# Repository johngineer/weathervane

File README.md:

# weathervane

Weathervane Digital Readout Hardware

February 1-2, 2015 (instead of watching the super bowl)

by John De Cristofaro (johngineer)

AVRdude fuse settings:  -U lfuse:w:0x6e:m -U hfuse:w:0xdf:m -U efuse:w:0x01:m

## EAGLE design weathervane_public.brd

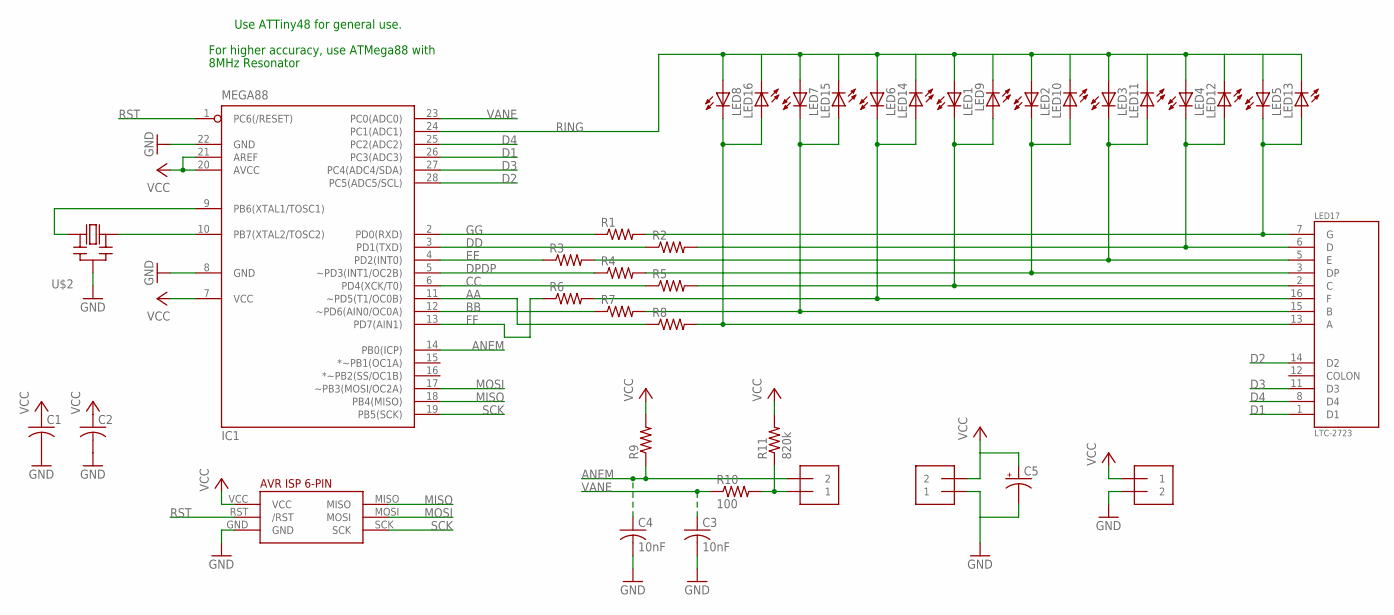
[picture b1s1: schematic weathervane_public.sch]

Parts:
C1, C2: C025_050X025
C3, C4: 10nF; C025_050X025
C5: C_POL2.5-6; E25-6
IC1: MEGA88; DIL28-3
J1, J2, J3: 1X2-3.5MM
LED1, LED2, LED3, LED4, LED5, LED6, LED7, LED8, LED9, LED10, LED11, LED12, LED13, LED14, LED15, LED16: LED5MM
LED17: LTC-2723
R1, R2, R3, R4, R5, R6, R7, R8, R9: R207/7; R_207/7
R10: 100; R_207/7
R11: 820k; R_207/7
U$1: AVR_ISP; AVR_ISP6
U$2: CERMOSCILL-THM; CERM_OSC

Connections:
A: LED8.K (C), LED16.A, LED17.13 (A), R8.2
AA: IC1.11 (~PD5(T1/OC0B)), R8.1
ANEM: C4.1, IC1.14 (PB0(ICP)), J1.2, R9.1
B: LED7.K (C), LED15.A, LED17.15 (B), R7.2
BB: IC1.12 (~PD6(AIN0/OC0A)), R7.1
C: LED1.K (C), LED9.A, LED17.2 (C), R5.2
CC: IC1.6 (PD4(XCK/T0)), R5.1
D: LED4.K (C), LED12.A, LED17.6 (D), R2.2
D1: IC1.26 (PC3(ADC3)), LED17.1 (D1)
D2: IC1.28 (PC5(ADC5/SCL)), LED17.14 (D2)
D3: IC1.27 (PC4(ADC4/SDA)), LED17.11 (D3)
D4: IC1.25 (PC2(ADC2)), LED17.8 (D4)
DD: IC1.3 (PD1(TXD)), R2.1
DP: LED2.K (C), LED10.A, LED17.3 (DP), R4.2
DPDP: IC1.5 (~PD3(INT1/OC2B)), R4.1
E: LED3.K (C), LED11.A, LED17.5 (E), R3.2
EE: IC1.4 (PD2(INT0)), R3.1
F: LED6.K (C), LED14.A, LED17.16 (F), R6.2
FF: IC1.13 (PD7(AIN1)), R6.1
G: LED5.K (C), LED13.A, LED17.7 (G), R1.2
GG: IC1.2 (PD0(RXD)), R1.1
GND: C1.2, C2.2, C3.2, C4.2, C5.-, IC1.8 (GND), IC1.22 (GND), J2.2, J3.1, U$1.GND, U$2.P$2 (GND)
MISO: IC1.18 (PB4(MISO)), U$1.MISO
MOSI: IC1.17 (~PB3(MOSI/OC2A)), U$1.MOSI
unnamed: IC1.10 (PB7(XTAL2/TOSC2)), U$2.P$3 (OUT)
unnamed: IC1.9 (PB6(XTAL1/TOSC1)), U$2.P$1 (IN)
unnamed: J1.1, R10.2, R11.1
RING: IC1.24 (PC1(ADC1)), LED1.A, LED2.A, LED3.A, LED4.A, LED5.A, LED6.A, LED7.A, LED8.A, LED9.K (C), LED10.K (C), LED11.K (C), LED12.K (C), LED13.K (C), LED14.K (C), LED15.K (C), LED16.K (C)
RST: IC1.1 (PC6(/RESET)), U$1.RST (/RST)
SCK: IC1.19 (PB5(SCK)), U$1.SCK
VANE: C3.1, IC1.23 (PC0(ADC0)), R10.1
VCC: C1.1, C2.1, C5.+, IC1.7 (VCC), IC1.20 (AVCC), IC1.21 (AREF), J2.1, J3.2, R9.2, R11.2, U$1.VCC

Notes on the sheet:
Use ATTiny48 for general use.
For higher accuracy, use ATMega88 with
8MHz Resonator

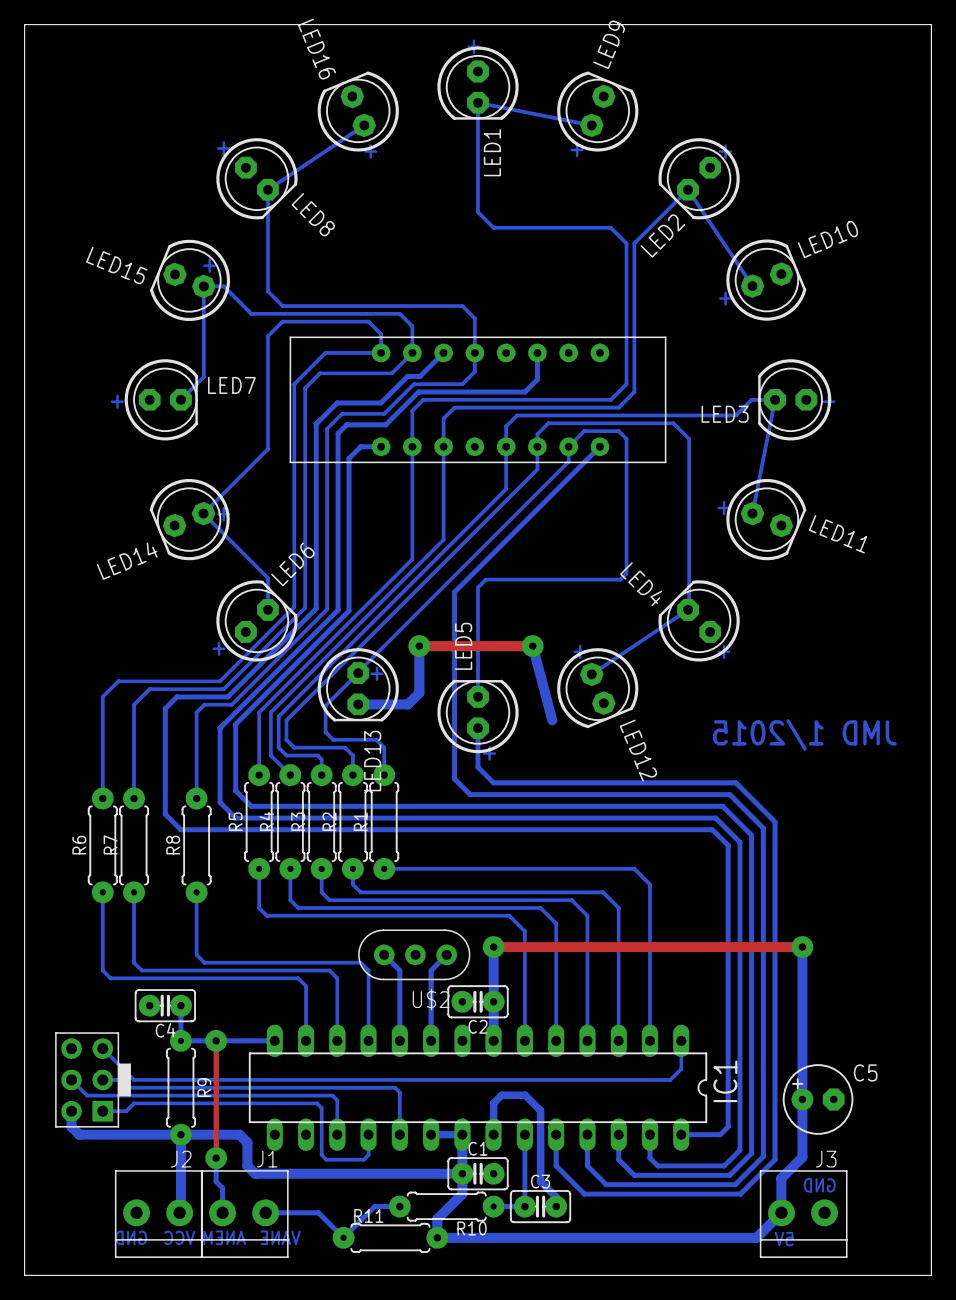
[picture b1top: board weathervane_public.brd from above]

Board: 2 copper layers, 73.7 x 101.6 mm, 39 parts (0 on the bottom side), 32 nets.

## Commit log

2015-02-06 first push
2015-02-06 added note to sch
2015-02-06 Revert "updated readme"
    This reverts commit 474d225439508ca28c871f1e648b65adc480109e.
2015-02-06 fixed error in brd
2015-02-06 fixed copper
